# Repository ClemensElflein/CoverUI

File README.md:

# CoverUI for [OpenMower](https://github.com/ClemensElflein/OpenMower)

## About

This repository contains the firmware files required to use the mowers CoverUI (ButtonBoard).

## Variants

1. Custom DIY CoverUI-PCB which replaces the stock (top-cover) PCB.<br>
 Please check the [Cover UI board assembly instructions](<https://openmower.de/docs/cover-ui-assembly/>) for more detailed infos.<br>
 Also available in [Vermut's Shop](https://shop.devops.care/10-openmower) (as part of his 'Upgrade Kit')
1. Stock YardForce CoverUI for the following models:
   1. Classic 500 (STM32 & GD32 MCU)
   2. Classic 500B (STM32 & GD32 MCU)
   3. SA/SC/NX-Type (10 Buttons, 12 LEDs), PCB labeled with RM-ECOW-V1.0.0 (STM32 MCU)
   4. SA/SC/NX-Type (9 Buttons, 11 LEDs), PCB labeled with RM-ECOW-V1.1.0 (STM32 & GD32 MCU)
   5. NX100i (18 Buttons, 3 LEDs, 256*64 Pixel LC-Display), PCB labeled with RM-EC3-V1.1 (STM32 MCU)
   6. SAxPro (Rev6) 6 Buttons 240*128 Pixel LC-Display (STM32 MCU)
   
    For this, you need to solder some cables and flash a modified firmware to it.<br>
    Please check the detailed [Stock CoverUI Readme](Firmware/CoverUI/YardForce/README.md) (as you've also the option to use your stock 'hall', 'stop' and 'rain' cables).

## License

Distributed under the MIT License. See [LICENSE](LICENSE) for more information.

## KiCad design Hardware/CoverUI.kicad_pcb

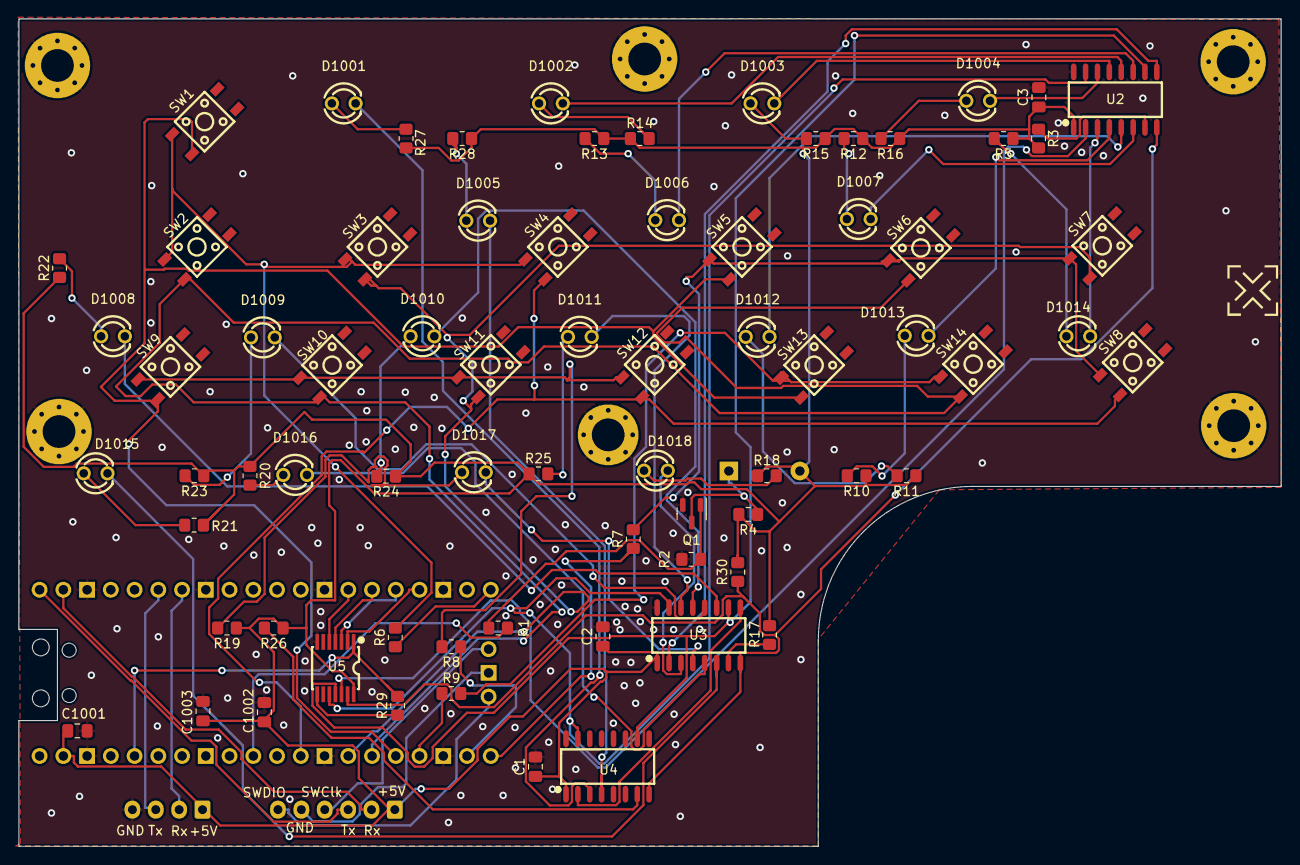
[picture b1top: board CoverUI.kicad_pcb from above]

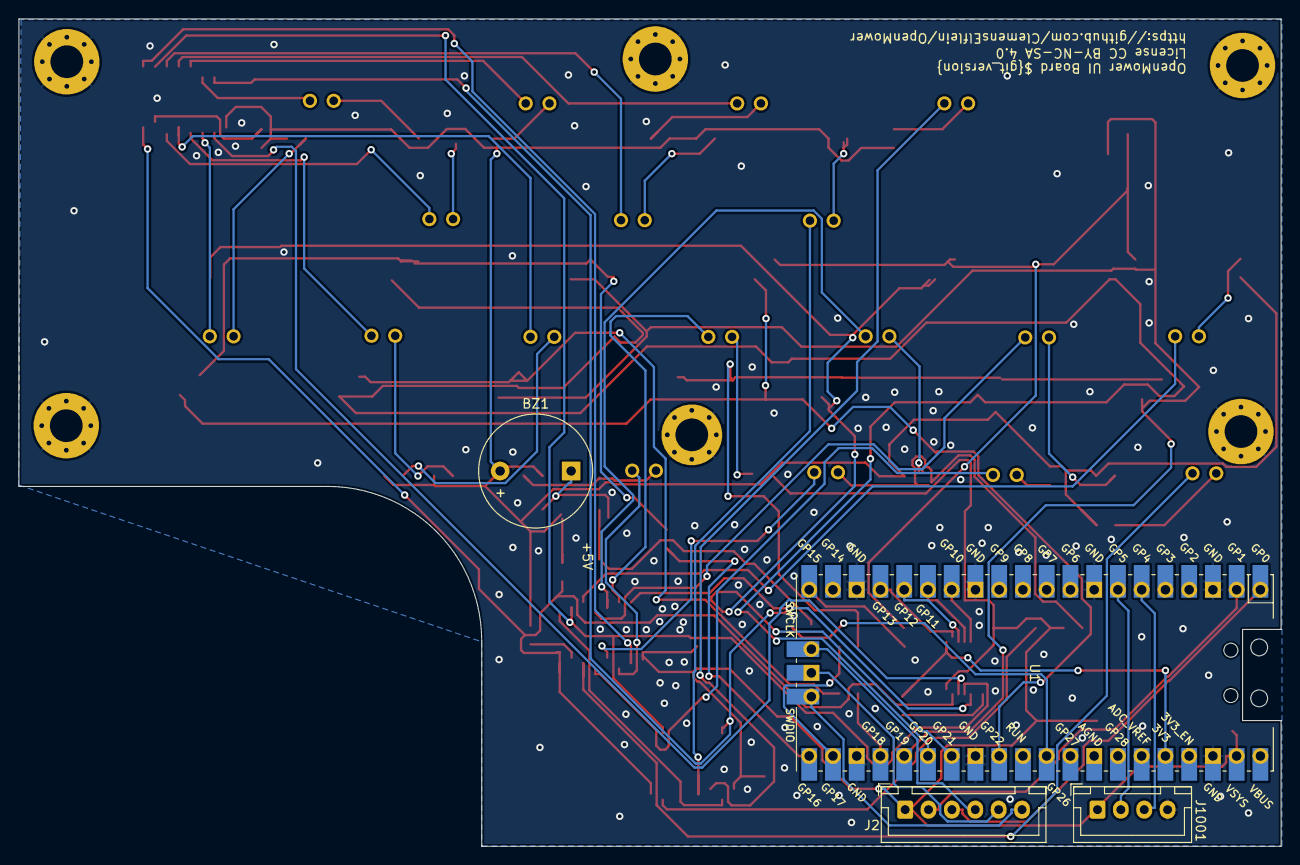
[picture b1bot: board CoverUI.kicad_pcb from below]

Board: 2 copper layers, 135.0 x 88.5 mm, 102 parts (4 on the bottom side), 75 nets.

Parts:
BZ1: Buzzer; Buzzer_12x9.5RM7.6
C1, C2, C3, C1001, C1002: 100nF; C_0805_2012Metric_Pad1.18x1.45mm_HandSolder
C1003: 1uF; C_0805_2012Metric_Pad1.18x1.45mm_HandSolder
D1001, D1002, D1003, D1004, D1005, D1006, D1007, D1008, D1009, D1010, D1011, D1012, D1013, D1014, D1015, D1016, D1017, D1018: 20mA 2V, Red; LED-TH_BD3.0-P2.54-FD
H1001, H1002, H1003, H1004, H1005, H1006: MountingHole_Pad; MountingHole_3.5mm_Pad_Via
J2: Conn_01x06_Male; JST_XH_B6B-XH-A_1x06_P2.50mm_Vertical
J1001: Conn_01x04_Male; JST_XH_B4B-XH-A_1x04_P2.50mm_Vertical
Q1: BSS138; SOT-23
R1, R4: 1k; R_0805_2012Metric_Pad1.20x1.40mm_HandSolder
R2: 47k; R_0805_2012Metric_Pad1.20x1.40mm_HandSolder
R3, R6, R7, R8, R9, R17, R26, R29, R30: 10k; R_0805_2012Metric_Pad1.20x1.40mm_HandSolder
R5, R10, R11, R12, R13, R14, R15, R16, R18, R19, R20, R21, R22, R23, R24, R25, R27, R28: 150; R_0805_2012Metric_Pad1.20x1.40mm_HandSolder
SP01, SP02, SP03, SP04, SP05, SP06, SP07, SP08, SP09, SP10, SP11, SP12, SP13, SP14, SP15, SP16: LedSpacer; LED_SPACER_3mm
SP17, SP18, SP20: LED_SPACER_3mm
SW1, SW2, SW3, SW4, SW5, SW6, SW7, SW8, SW9, SW10, SW11, SW12, SW13, SW14: SW_MEC_5G; SW-SMD_4P-L4.5-W4.5-P3.00-LS7.0
U1: Raspberry-Pico; RPi_Pico_SMD_TH
U2, U3, U4: TPIC6C596DRG4; SOIC-16_L10.8-W4.5-P1.27-LS6.8-BL
U5: RS0104YQ; TSSOP-14_L5.0-W4.4-P0.65-LS6.4-BL

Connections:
+3.3V: R29.2, U1.36 (3V3), U5.1 (VCCA)
+5V: BZ1.2 (+), C1.1, C2.1, C3.1, C1001.1, C1002.1, C1003.1, J2.1, J1001.1, R3.1, R4.2, R5.1, R10.1, R11.1, R12.1, R13.1, R14.1, R15.1, R16.1, R17.1, R18.1, R19.1, R20.1, R21.1, R22.1, R23.1, R24.1, R25.1, R26.1, R27.1, R28.1, R30.2, U1.39 (VSYS), U2.1 (VCC), U3.1 (VCC), U4.1 (VCC), U5.14 (VCCB)
/LEDmux/G: R30.1, U2.8 (~G), U3.8 (~G), U4.8 (~G), U5.13 (B1)
/LEDmux/G_3.3V: U1.17 (GPIO13), U5.2 (A1)
/LEDmux/RCK: U2.10 (RCK), U3.10 (RCK), U4.10 (RCK), U5.11 (B3)
/LEDmux/RCK_3.3V: U1.15 (GPIO11), U5.4 (A3)
/LEDmux/SER: U2.2 (SER/IN), U5.12 (B2)
/LEDmux/SER_3.3V: U1.16 (GPIO12), U5.3 (A2)
/LEDmux/SRCK: U2.15 (SRCK), U3.15 (SRCK), U4.15 (SRCK), U5.10 (B4)
/LEDmux/SRCK_3.3V: U1.14 (GPIO10), U5.5 (A4)
/RaspberryPico/GP15: R6.1, U1.20 (GPIO15)
/RaspberryPico/GP16: R7.1, U1.21 (GPIO16)
/RaspberryPico/GP17: R8.1, U1.22 (GPIO17)
/RaspberryPico/GP18: R9.1, U1.24 (GPIO18)
/RaspberryPico/GP19: SW1.3 (B), SW5.3 (B), SW9.3 (B), SW13.3 (B), U1.25 (GPIO19)
/RaspberryPico/GP20: SW2.3 (B), SW6.3 (B), SW10.3 (B), SW14.3 (B), U1.26 (GPIO20)
/RaspberryPico/GP21: SW3.3 (B), SW7.3 (B), SW11.3 (B), U1.27 (GPIO21)
/RaspberryPico/GP22: SW4.3 (B), SW8.3 (B), SW12.3 (B), U1.29 (GPIO22)
/RaspberryPico/GP26: R1.1, U1.31 (GPIO26_ADC0)
/RaspberryPico/PiCo_RX: J1001.2, U1.7 (GPIO5)
/RaspberryPico/PiCo_TX: J1001.3, U1.6 (GPIO4)
GND: C1.2, C2.2, C3.2, C1001.2, C1002.2, C1003.2, H1001.1, H1002.1, H1003.1, H1004.1, H1005.1, H1006.1, J1001.4, Q1.2 (S), R2.2, U1.3 (GND), U1.8 (GND), U1.13 (GND), U1.18 (GND), U1.23 (GND), U1.28 (GND), U1.38 (GND), U2.16 (GND), U3.16 (GND), U4.16 (GND), U5.7 (GND)
unnamed: BZ1.1 (-), Q1.3 (D), R4.1
unnamed: D1001.1 (A), R27.2
unnamed: D1001.2 (K), U4.3 (DRAIN0)
unnamed: D1002.1 (A), R14.2
unnamed: D1002.2 (K), U2.12 (DRAIN5)
unnamed: D1003.1 (A), R15.2
unnamed: D1003.2 (K), U2.13 (DRAIN6)
unnamed: D1004.1 (A), R16.2
unnamed: D1004.2 (K), U2.14 (DRAIN7)
unnamed: D1005.1 (A), R28.2
unnamed: D1005.2 (K), U4.4 (DRAIN1)
unnamed: D1006.1 (A), R13.2
unnamed: D1006.2 (K), U2.11 (DRAIN4)
unnamed: D1007.1 (A), R12.2
unnamed: D1007.2 (K), U2.6 (DRAIN3)
unnamed: D1008.1 (A), R22.2
unnamed: D1008.2 (K), U3.11 (DRAIN4)
unnamed: D1009.1 (A), R23.2
unnamed: D1009.2 (K), U3.12 (DRAIN5)
unnamed: D1010.1 (A), R24.2
unnamed: D1010.2 (K), U3.13 (DRAIN6)
unnamed: D1011.1 (A), R25.2
unnamed: D1011.2 (K), U3.14 (DRAIN7)
unnamed: D1012.1 (A), R11.2
unnamed: D1012.2 (K), U2.5 (DRAIN2)
unnamed: D1013.1 (A), R10.2
unnamed: D1013.2 (K), U2.4 (DRAIN1)
unnamed: D1014.1 (A), R5.2
unnamed: D1014.2 (K), U2.3 (DRAIN0)
unnamed: D1015.1 (A), R21.2
unnamed: D1015.2 (K), U3.6 (DRAIN3)
unnamed: D1016.1 (A), R20.2
unnamed: D1016.2 (K), U3.5 (DRAIN2)
unnamed: D1017.1 (A), R19.2
unnamed: D1017.2 (K), U3.4 (DRAIN1)
unnamed: D1018.1 (A), R18.2
unnamed: D1018.2 (K), U3.3 (DRAIN0)
unnamed: J2.2, U1.2 (GPIO1)
unnamed: J2.3, U1.1 (GPIO0)
unnamed: J2.4, U1.41 (SWCLK)
unnamed: J2.5, U1.42 (GND)
unnamed: J2.6, U1.43 (SWDIO)
unnamed: Q1.1 (G), R1.2, R2.1
unnamed: R3.2, U2.7 (~CLR)
unnamed: R6.2, SW1.1 (A), SW2.1 (A), SW3.1 (A), SW4.1 (A)
unnamed: R7.2, SW5.1 (A), SW6.1 (A), SW7.1 (A), SW8.1 (A)
unnamed: R8.2, SW9.1 (A), SW10.1 (A), SW11.1 (A), SW12.1 (A)
unnamed: R9.2, SW13.1 (A), SW14.1 (A)
unnamed: R17.2, U3.7 (~CLR)
unnamed: R26.2, U4.7 (~CLR)
unnamed: R29.1, U5.8 (OE)
unnamed: U2.9 (SER/OUT), U3.2 (SER/IN)
unnamed: U3.9 (SER/OUT), U4.2 (SER/IN)

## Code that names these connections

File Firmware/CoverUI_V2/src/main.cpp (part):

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
#define UNUSED_PIN p14

mbed::DigitalOut PIN_RCK = mbed::DigitalOut(p11);
mbed::DigitalOut PIN_SER = mbed::DigitalOut(p12);
mbed::DigitalOut PIN_SRCK = mbed::DigitalOut(p10);
mbed::DigitalOut PIN_G = mbed::DigitalOut(p13);
mbed::DigitalOut no_pin = DummyOut(UNUSED_PIN);

ShiftRegister shiftRegister = ShiftRegister(
        PIN_SRCK,
        PIN_SER,
        PIN_RCK,
        no_pin,
        PIN_G
);
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
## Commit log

2023-04-20 Initial version
2023-04-21 Align LED IDs
2023-04-21 Align LED order to LowLevel code
2023-04-23 Improve INT priorities and unused GPIOs
2023-04-23 Correct LED_NUM_x defines
2023-04-24 Restructure timer, INT priorities, Animation, add LED sequences
2023-04-25 Readme & FW binary
2023-04-25 Fixed some typo failures
2023-04-26 Add debug probe infos
2023-04-26 Fix image align
2023-04-27 Add GD32 exception
2023-04-27 feat: cover UI HW 1.1.0
2023-04-27 chore: rename to Hardware
2023-04-27 chore: basic CI
2023-04-27 feat: CoverUI 2.0
2023-04-27 chore(ci): firmware builder
2023-04-29 Update flash instructions
2023-04-30 LEDs & Timer work. GD32 partly
2023-04-30 Moved logic from main() to loop()
2023-04-30 Start Button support
2023-05-01 Eval STM32 bootup issue
2023-05-01 STM32 Timer (prep. for GD32), Picoprobe, cleanup
2023-05-01 Actualized some docs and readme
2023-05-02 Done HW-Serial, but Arudino Implementation is slow and miss UART ISR
2023-05-03 chore: dummy commit to push release
2023-05-04 Finish LEDs, Timer & HardwareSerial
2023-05-04 Cleanup
2023-05-06 Finish buttons for STM32
2023-05-06 Switch GD32 timer to general purpose timer
2023-05-07 deploy: c7820c56d3d04c38fefb832e54f7dda454ebd3c2
2023-05-07 Finish GD32 button support
2023-05-07 Actualize flash info
2023-05-09 Rain & Hall functional & generic rain measurements
2023-05-09 Finish Rain class
2023-05-09 Rain docs
2023-05-11 Finish emergency handling
2023-05-11 Documentation
2023-05-11 Cleanup & firmware/MOD syntax
2023-05-11 Split MODs into env variants
2023-05-11 FW versioning
2023-05-11 Common style
2023-05-13 Finalize, cleanup, docs
2023-05-13 PR cleanup
2023-05-23 Stock rain sensor workings well in practice
2023-05-24 Fix GD32 (floating) INPUT
2023-05-24 Correct firmware naming
2023-05-28 Fix absolute link
2023-06-15 Fix typo & add/correct some LED/Button usage infos
2023-08-15 YFC500B Schematics
2023-08-15 Stock FW dump
2023-08-15 Classic 500B documentation
2023-09-01 First tests & schematics
2023-09-01 Reorganized schematics
2023-09-01 Stock FW backup
2023-09-01 Add minimalistic infos
2023-09-01 Add buttons
2023-09-01 Rename yfc500 folder to more common YardForce
2023-09-03 Fix: Actually Register SW14 for button press events
    SW14 has never been registered for button press events. The loop ignores it, because it's missing the last iteration.
    This was most likely a copy & paste mistake from the TEST_MODE code below where SW14 is handled specially and not by a loop iterating over all buttons.
2023-09-11 Restructure for common C500 & SAxPRO usage
2023-09-11 Initial SAxPRO/LVGL
2023-09-11 Fix SAxPRO build
2023-09-11 Restructure into LedSymbol & Bar widgets
2023-09-12 Add Text-Ticker Widget
2023-09-12 Fix wrong inverse color handling
2023-09-12 Finalize top bar icons
2023-09-12 Switch to low-priority hardware-timer based lv_timer_handler()
2023-09-13 Add touch panel
2023-09-13 Add flash and some cleanup
2023-09-14 Switch to getopt and add --lcd option
2023-09-15 Finish LED state conversions
2023-09-15 Fix changed path
2023-09-15 Cosmetic schematic changes
2023-09-16 Minor improvements, changes, cleanup
2023-09-16 Minor LED-2-Symbol adaptions
2023-09-16 Fix and clean debouncer
2023-09-22 Major state handling. Fix backlight timeout malfunction
2023-09-23 Separate backlight timeout, add emergency clear handling
2023-09-23 Backlight on cover-open
2023-09-23 Fix emergency clear
2023-09-24 Adapt charge bar
2023-09-24 GD32 hwtimer fix
2023-09-27 Final optimizations
2023-09-27 Add volume up, down and language switch
2023-09-27 Binaries
2023-09-27 Add SAxPRO
2023-09-27 Fix optional mod syntax
2023-09-27 Skip .vscode folder
2023-10-22 Add schematics
2023-10-22 Original FW backup
2023-10-25 LEDcontrol base- & sub-class separation for RM-ECOW-V100
2023-10-25 Nifty restructuration
2023-10-29 Restructured Button code
2023-10-29 Reimplemented magic buttons and finished button & LED restructuration
2023-10-30 Split up Hardware Mods and added RM-ECOW-V1.0.0
2023-10-30 Evaluated Hall Support
2023-10-30 Fixed links
2023-10-31 Started backport of C500- STM32 & GD32. Broken!
2023-10-31 Finished backport of C500- STM & GD32
2023-10-31 Passed by reference instead value
2023-10-31 Adapted Emergency for common C500 & RMECOWV100 usage
2023-11-01 Add stock-firmware builds to CI
2023-11-01 Add stock-firmware to CI job 'tagged-release'
2023-11-02 Refactored again for SAxPRO backport. SAxPRO code isn't working yet!
2023-11-07 Refactoring done. SAxPRO compiles. Added Hatch class
2023-11-07 Fix HALL_MOD build
2023-11-07 New binary location
2023-11-09 Fix model typo
2023-11-12 Finished SAxPRO and refactoring
2023-11-12 Some final fixes
2023-11-12 Fix packet
2023-11-12 Fix out of bounds array access
2023-11-12 Configure std LEDs as NC-LEDs
2023-11-12 Final RL fixes
2023-11-13 Fix docking states and backlight handling
2023-11-14 Fix GD32F3x PLL
2023-11-14 Activate boot anim, adjust charge min. value
2023-11-14 Fix compile error
2023-11-14 Some typo, version, link
2023-11-14 Fix NX80i naming
2023-11-14 OEM FW backup
2023-11-19 RM-EC3-V1.1 schematics
2023-11-25 Finish ST75256 controller driver
2023-11-27 NX100i general done
2023-11-27 Moved ST75256 to controller namespace
2023-11-28 Change namespace
2023-11-28 Made display a abstract Display class
2023-11-28 Refactor display as abstract Display class
2023-11-28 Fix missing subscription
2023-11-28 Fix widget arrangement
2023-11-28 Add emergencies STOP & HALL
2023-11-29 Fix emergency, finish NX100i implementation
2023-11-29 Final cosmetic changes
2023-11-29 Adapt SAxPRO to new structure
2023-11-29 Add NX100i to the docs
2023-11-29 Minor corrections
2023-11-29 CI build of NX100i FW
2023-11-29 Actualized meaning of the LEDs for NX100i
2023-12-02 Optimize UC1698 and flush_cb()
2024-04-14 Remove "Next Language" info
2024-06-30 Add circuit diagram
2024-06-30 Fix once-only header identifier
2024-06-30 Support SA650 RM-ECOW-V1.1.0 (9-Button/11-LED) CoverUI
2024-06-30 Change magic button for SA650
2024-06-30 Change alive LED to be software driven (non hwtimer)
2024-06-30 Add Buttons & LEDs for SA650
2024-07-01 Fix countdown anim
2024-07-01 Fix emergency clear LED countdown
2024-07-02 Add SA650
2024-07-02 Fix some links
2024-07-02 Fix SA650 ToC link
2024-07-02 Add new SA650 CoverUI
2024-07-02 Add new model info
2024-07-05 SA600/900 (RM-ECOW-V1.1.0) support (#10)
    * Add schematics
    * Original FW backup
    * LEDcontrol base- & sub-class separation for RM-ECOW-V100
    * Nifty restructuration
    * Restructured Button code
    * Reimplemented magic buttons and finished button & LED restructuration
2024-09-24 Add RM-ECOW-V1.1.0 STM32 support
2024-09-24 Remove Picoprobe support
2024-09-24 Add new variant to CI
2024-09-29 Add MOD_HALL to RM-ECOW-V1.0.0
2024-09-29 Restructure docs and add HALL support to RM-ECOW-V1.0.0
2024-09-30 Fix heap overflow
2024-09-30 Some minor adaptions
2024-10-03 Refactor stock YF part
2024-10-03 Fix missing artifact
2024-10-03 Support for SA900 CoverUI with STM32 MCU and ... (#11)
    * Add RM-ECOW-V1.1.0 STM32 support
    * Remove Picoprobe support
    * Add new variant to CI
    * Add MOD_HALL to RM-ECOW-V1.0.0
    * Restructure docs and add HALL support to RM-ECOW-V1.0.0
    * Fix heap overflow
2025-06-23 Improve main and Yardforce 500 docs
2025-06-23 Add missing changes
2025-11-21 Dummy commit to trigger CI
2025-11-21 Updated CI action versions for cache and upload-artifact
2025-11-21 newline for debug output

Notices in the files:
Hardware/CoverUI.kicad_pcb:
License CC BY-NC-SA 4.0
README.md:
License: MIT
